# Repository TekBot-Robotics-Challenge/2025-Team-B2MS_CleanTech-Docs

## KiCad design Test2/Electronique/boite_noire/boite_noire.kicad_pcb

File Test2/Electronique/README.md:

# Introduction
Dans les systèmes embarqués modernes, la collecte et l’analyse de données en temps réel sont essentielles pour le suivi et la sécurité des équipements, notamment dans des domaines critiques comme l’automobile, l’aviation ou le ferroviaire. S’inspirant du fonctionnement des boîtes noires utilisées dans ces industries, ce projet a pour objectif de concevoir un système embarqué capable d’enregistrer et de transmettre en temps réel des données de mouvement (vitesse et orientation) à l’aide d’un capteur inertiel. Les informations sont ensuite visualisées sur une station de contrôle via un écran LCD.
Ce projet s’inscrit dans le cadre du Tekbot Robotics Challenge et fait appel à plusieurs compétences majeures : programmation directe des microcontrôleurs ATmega328P sans utiliser de carte Arduino, communication via le protocole I2C, conception de circuits imprimés avec KiCAD, réalisation d’un boîtier cubique de 7 cm, intégration matérielle sur veroboard ou PCB, ainsi que la conception d’une alimentation spécifique.
# Sommaire

- [cahier des charges ](#Cahier-des-charges)
- [Schéma synoptique](#Schéma-synoptique)
- [Réalisation du PCB](#Réalisation-du-PCB)
- [Description fonctionnelle des différents blocs du système](#Description-fonctionnelle-des-différents-blocs-du-système)
- [La communication I2C](#La-communication-I2C)
- [Etapes de validation avant PCB](#Etapes-de-validation-avant-PCB) 
  
# Cahier des charges

## Objectifs fonctionnels
- Lire les données de vitesse et d’orientation à l’aide du MPU6050
- Utiliser le microcontrôleur ATmega328P sans carte Arduino
- Concevoir un circuit imprimé (PCB) et une alimentation autonome
- Transmettre les données à une station de contrôle via I2C
- Afficher les données sur un écran LCD en mode 4 bits

## Contraintes techniques
- Le cube doit mesurer 7x7x7 cm, avec une face ouverte pour voir le circuit
- Le microcontrôleur du cube agit en **maître I2C**
- Le microcontrôleur de la station agit en **esclave I2C**
- Alimentation externe obligatoire, hors du cube
- Schéma et PCB réalisés avec **KiCad**

## Matériel utilisé

- [ATmega328P](https://ww1.microchip.com/downloads/en/DeviceDoc/Atmel-7810-Automotive-Microcontrollers-ATmega328P_Datasheet.pdf) ×2  
- [MPU6050](https://invensense.tdk.com/wp-content/uploads/2015/02/MPU-6000-Datasheet1.pdf)  
- [LCD 16x2 (mode 4 bits)](https://www.gotronic.fr/pj2-sbc-lcd16x2-fr-1441.pdf?srsltid=AfmBOopmg8VyH8PQXxRcqE7GEvoyRwGRHeKVU9ZsKwGmKu13oZXhPhaJ)  
- Alimentation

# Schéma synoptique
Ce système embarqué est composé de deux unités : une boîte noire et une station de contrôle, connectées via le bus I2C. La boîte noire comprend un capteur MPU6050 qui détecte les mouvements de la main et envoie les données à un microcontrôleur ATmega328P configuré en maître. Celui-ci traite les données et les transmet à la station de contrôle, où un autre ATmega328P, configuré en esclave, les reçoit. Les informations sont ensuite affichées sur un écran LCD. Chaque unité est alimentée séparément par une source de 5V.

# Description fonctionnelle des différents blocs du système
## Bloc d’alimentation
## 1. Fonction principale
Ce bloc a pour objectif de fournir une tension continue et stable de 5V nécessaire au fonctionnement des différents composants électroniques du système, notamment le capteur MPU6050, les microcontrôleurs ATmega328P et l'écran LCD.
## 2. Fonctionnement
On utilise trois batteries de Li-Ion 3,7V rechargeables montées en série pour obtenir environ 12V.  
Le régulateur L7805 reçoit ce 12V en entrée (Vin) et fournit du 5V en sortie (Vout).  
Deux condensateurs (330nF et 100nF) sont utilisés pour stabiliser la tension et filtrer les parasites.
- 330nF à l’entrée
- 100nF à la sortie

📌 Le schéma suivant illustre ce montage :

   La simulation sur proteus 
   Les condensateurs de filtrage ont été omis dans ce schéma pour simplifier la représentation, bien qu’ils soient indispensables en pratique pour assurer la stabilité et réduire le bruit.

## Bloc d’entrée(dans la boite noire)

Nous avons choisi le capteur MPU6050 parce qu’il intègre un accéléromètre et un gyroscope dans un seul composant. Cela permet de mesurer les mouvements et les rotations de la main avec précision. Il est facile à utiliser grâce au protocole I2C, et il fonctionne bien avec le microcontrôleur ATmega328P. En plus, il est peu coûteux et largement utilisé dans les projets embarqués. D’autres capteurs peuvent faire un travail similaire, comme le MPU9250 (qui ajoute un magnétomètre), le LSM6DS3 (plus récent et plus économe), ou le ADXL34

## Bloc de commande(dans la boite noire)
### 🛠️ Étape 1 : Prise en main du microcontrôleur ATmega328P

Avant de démarrer le système complet, l’équipe s’est d’abord focalisée sur le microcontrôleur ATmega328P. L’objectif était de comprendre pleinement sa structure interne, ses broches, ainsi que la manière de le configurer et de le simuler.

Nous avons étudié ses principales caractéristiques et son brochage :

- Le format DIP à 28 broches, comme dans les cartes Arduino Uno
- Les broches d’E/S numériques D0 à D13, pour piloter des LED, relais, etc.
- Les entrées analogiques A0 à A5, pour la lecture de capteurs
- L’interface I2C via SDA (PC4) et SCL (PC5)
- La communication série UART via TX (PD1) et RX (PD0)
- Les broches d’alimentation : VCC, GND, AVCC, AREF
- La broche RESET, généralement tirée à l’état haut via une résistance
- Les broches XTAL1/XTAL2 pour le quartz (utilisé plus tard)

Ces éléments nous ont permis de préparer une simulation fiable sous Proteus pour la suite du projet.

### 🧪 Étape 2 : Simulation basique de l’ATmega328P dans Proteus

Après avoir étudié la configuration du microcontrôleur, nous avons réalisé une première simulation simple sous Proteus, afin de valider son fonctionnement dans un environnement simulé.

À ce stade :

- Nous n'avons pas utilisé les connexions d’alimentation (VCC/AVCC) ni de quartz externe, car elles ne sont pas obligatoires pour les logiques simples dans Proteus.
- Nous nous sommes concentrés sur le comportement des broches dans un exemple réel.

#### Scénario de simulation :
Nous avons conçu un système simple dans lequel :

- Un bouton poussoir est connecté à une entrée numérique.
- Lorsqu’on appuie sur le bouton, l’ATmega active un relais via une sortie numérique.
- Ce relais commande une lampe LED 12V, simulant une charge réelle.

Le code Arduino correspondant a été compilé dans l’IDE Arduino, puis le fichier .hex généré a été intégré dans Proteus pour tester le comportement du circuit.

https://github.com/user-attachments/assets/d1cc5dd5-9109-4822-be6e-245693643c00
#### Observations :
- Lorsque le bouton est pressé, le relais s’active et allume la LED.
- Le comportement observé est conforme à la logique attendue et cohérente.
## Bloc d’affichage de la station du controle
Pour l’affichage des données au niveau de la station de contrôle, nous avons opté pour un écran LCD équipé d’un module I2C. Ce choix permet de simplifier le montage électronique en réduisant considérablement le nombre de connexions nécessaires entre le microcontrôleur et l’écran. Grâce à cette interface, seules deux lignes (SDA et SCL) suffisent pour transmettre les informations, ce qui laisse davantage de broches disponibles pour d’autres composants. L’écran LCD I2C assure ainsi une lecture claire et en temps réel des données de vitesse et d’orientation envoyées par la boîte noire.  

# La communication I2C
Ce document constitue une présentation détaillée et approfondie du protocole **I2C (Inter-Integrated Circuit)**, qui est un standard de communication série synchrone très répandu dans l’électronique embarquée. Ce protocole facilite l’échange d’informations entre un ou plusieurs maîtres et plusieurs périphériques esclaves en utilisant seulement deux fils, simplifiant ainsi les connexions matérielles tout en assurant une communication fiable et efficace.  

## ⚙️ Principe de fonctionnement
[Protocole I2C](https://fr.wikipedia.org/wiki/I2C) (Inter-Integrated Circuit), développé par Philips (aujourd’hui NXP) dans les années 1980, est un standard mondial pour la communication série entre circuits intégrés, surtout dans les systèmes embarqués. Il utilise un bus bidirectionnel à deux fils : SDA pour les données et SCL pour l’horloge, permettant à plusieurs périphériques de partager le même canal tout en gérant précisément l’accès.  
Contrairement à des protocoles comme SPI, I2C minimise le nombre de connexions nécessaires, ce qui simplifie le routage sur circuit imprimé et réduit les coûts.   Ce protocole est largement utilisé dans des domaines variés : automobile, domotique, informatique, etc.  
I2C fonctionne selon un modèle.[maître-esclave](https://www.ionos.fr/digitalguide/serveur/know-how/le-principe-master/slave): un ou plusieurs maîtres contrôlent la communication, et les esclaves répondent aux requêtes. Chaque communication commence par une condition **Start**, suivie de **l’adresse de l’esclave** et d’un bit de direction (lecture/écriture). Les données sont ensuite échangées octet par octet, chaque octet étant confirmé par **un bit d’acquittement**(ACK). La communication se termine par une condition **Stop**, qui libère le bus.  
Techniquement, I2C utilise des lignes ouvertes (open-drain) : les dispositifs ne peuvent que tirer les lignes vers le bas, tandis que des résistances pull-up maintiennent le niveau haut par défaut. Cela évite les conflits, notamment en mode multi-maîtres.  
Enfin, I2C offre une grande flexibilité en termes de vitesse, du mode standard (100 kHz) au mode rapide (jusqu’à 3,4 MHz) et au-delà dans certaines variantes propriétaires.  

### 🔹 Prise de contrôle du bus

La prise de contrôle du bus par un maître débute par une **condition Start (S)**, qui est un événement distinctif sur le bus. Cette condition correspond à une transition sur la ligne SDA de l’état haut à l’état bas, alors que la ligne SCL est maintenue à l’état haut. Cette séquence particulière est détectée par tous les périphériques connectés au bus, qui entrent alors en mode écoute, prêts à recevoir des données.  

La condition Start joue un rôle fondamental : elle marque l’exclusivité du maître sur le bus, ce qui évite les collisions ou l’interférence avec d’autres maîtres éventuels. Elle sert aussi de synchronisation initiale à la transmission de données, en assurant que tous les appareils sont synchronisés sur le début de la communication.  

Les résistances pull-up sur les lignes SDA et SCL maintiennent ces lignes à un état logique haut par défaut, garantissant ainsi que le bus est en repos quand aucune communication n’a lieu.

## 🖼️ Image : BUS I2C 

## 🖼️ Image : condition start

---

### 🔹 Transmission d'un octet

La transmission des données sur le bus I2C s’effectue par octets (8 bits). Chaque bit est transmis séquentiellement, en commençant par le bit le plus significatif (MSB).  

Le protocole impose que chaque bit soit placé sur la ligne SDA pendant que la ligne SCL est à l’état bas. Ensuite, la ligne SCL passe à l’état haut, moment où le récepteur lit la valeur présente sur la ligne SDA. Lorsque la ligne SCL redescend à l’état bas, l’émetteur peut placer le bit suivant sur SDA, et ainsi de suite.  

Après l’envoi des 8 bits d’un octet, la ligne SDA est libérée pendant le 9e cycle d’horloge. C’est alors au récepteur de signaler par un bit d’acquittement (ACK) s’il a correctement reçu l’octet, en tirant la ligne SDA à l’état bas. S’il ne tire pas SDA à zéro, un bit de non-acquittement (NACK) est détecté, ce qui indique que la communication doit être interrompue ou qu’une erreur s’est produite.  

Ce mécanisme d’**ACK/NACK** est crucial car il assure la fiabilité des transmissions, permettant au maître de savoir si l’esclave est disponible et prêt à recevoir ou envoyer des données.

---

### 🔹 Transmission d'une adresse

Après la condition Start, le maître envoie un octet d’adresse pour identifier l’esclave avec lequel il souhaite communiquer. L’adresse est généralement codée sur 7 bits, suivis d’un bit R/W indiquant si la transaction sera une lecture ou une écriture.  

Le protocole prévoit aussi une extension 10 bits pour les réseaux comportant un grand nombre de périphériques, mais cette extension est moins fréquemment utilisée.  

Tous les périphériques esclaves surveillent le bus et comparent l’adresse reçue avec leur propre adresse. Celui qui reconnaît son adresse répond alors par un bit ACK en tirant la ligne SDA à l’état bas pendant le 9e bit. Les autres esclaves restent silencieux jusqu’à la prochaine séquence.  

Cette étape est essentielle car elle garantit que seules les communications destinées à un périphérique spécifique sont traitées, évitant ainsi toute interférence entre plusieurs périphériques sur le même bus.
## 🖼️ Image : transmission d'une adresse  

---

### 🔹 Écriture d'une donnée

Une fois l’adresse reconnue par l’esclave, la phase de transfert des données peut commencer. Le maître transmet alors les octets de données à l’esclave, chaque octet étant suivi d’un bit ACK envoyé par l’esclave pour confirmer la bonne réception.  

Le protocole permet d’envoyer autant d’octets que nécessaire dans une même communication, ce qui permet des transferts efficaces et continus.  

Pour terminer la communication, le maître génère une condition **Stop (P)**, qui correspond à une transition de la ligne SDA de l’état bas à l’état haut alors que la ligne SCL est haute. Cette séquence indique à tous les périphériques que la transmission est terminée et que le bus est libéré pour une autre communication.  

Il existe également une condition **Restart**, qui est une condition Start générée sans condition Stop préalable, permettant de chaîner plusieurs opérations sur le même bus sans interruption.  
## 🖼️ Image : transmission d'une donnee

## 🖼️ Image : condition stop

---

### 🔹 Arbitration

Le protocole I2C est conçu pour supporter un mode multi-maîtres, où plusieurs maîtres peuvent tenter d’accéder au bus simultanément. Pour éviter les conflits, un mécanisme d’arbitrage est mis en place.  

Lorsqu’un maître commence à transmettre, il surveille la ligne SDA et la compare avec ce qu’il souhaite envoyer. Si un maître détecte que la ligne SDA est forcée à l’état bas par un autre maître alors qu’il tente de la maintenir haute, il comprend qu’il a perdu l’arbitrage et abandonne immédiatement la transmission, laissant le bus libre au maître dominant.  

Ce mécanisme garantit qu’aucune collision électrique ne se produit sur le bus et que seule une source transmet à un instant donné. C’est une des forces du protocole I2C, qui permet une coexistence harmonieuse de plusieurs maîtres sur un même bus.
## 🖼️ Image : arbitrage

### 🔹 Clock Stretching

Le clock stretching est une fonctionnalité du protocole I2C qui permet à un esclave de ralentir temporairement la communication lorsqu’il n’est pas prêt à envoyer ou recevoir des données. Cela se fait en gardant la ligne SCL à l’état bas (LOW), empêchant ainsi le maître de continuer à envoyer des impulsions d’horloge. Une fois que l’esclave est prêt, il libère la ligne SCL, permettant au maître de reprendre la transmission. Cette technique est utile, par exemple, lorsque le capteur a besoin de plus de temps pour traiter ou préparer les données. Le maître doit respecter cet étirement d’horloge pour éviter des erreurs de communication.  

## 🖼️ Image : clock stretching

---
## 📡 Communication I2C entre MPU6050 et ATmega328P
Dans notre projet, le microcontrôleur **ATmega328P** communique avec le capteur **MPU6050** à l’aide du protocole **I2C**. Ce protocole permet de transmettre les données d’accélération et de rotation via deux fils (`SDA` et `SCL`). Le **MPU6050** agit comme **esclave**, et l’**ATmega328P** comme **maître**.

---

### 🔹 Fonctionnement de la liaison I2C

La connexion matérielle entre le MPU6050 et l’ATmega328P s’effectue via le protocole I2C (Inter-Integrated Circuit), qui utilise deux lignes de communication :   
- SDA (Serial Data Line) : ligne bidirectionnelle pour l’échange des données, connectée à la broche PC4 de l’ATmega328P.    
- SCL (Serial Clock Line) : ligne d’horloge générée par le maître, connectée à la broche PC5 de l’ATmega328P.

Sur le bus I2C, le dispositif qui initie la communication est appelé maître, tandis que celui qui répond s’appelle esclave. Dans notre cas :    
L’ATmega328P joue le rôle de maître, c’est lui qui contrôle le bus, génère l’horloge, et initie les échanges.    
Le MPU6050 est l’esclave, il attend que le maître lui demande des données spécifiques.    
Le maître démarre la communication en envoyant une adresse unique correspondant à l’esclave (ici l’adresse I2C du MPU6050, généralement 0x68), suivie d’une commande indiquant quel registre ou donnée il souhaite lire.  
                          
| ATmega328P | MPU6050 |
|------------|---------|
| PC4 (SDA)    | SDA     |
| PC5 (SCL)    | SCL     |
| VCC        | 5V  |
| GND        | GND     |
| 🔧 Pull-up | Recommandé : 4.7kΩ sur SDA et SCL |  

## 🖼️ Image : liaison-i2c-entre-mpu6050-et-atmega328p

---

### 🔹 Envoi des commandes et réception des données

La communication suit ce processus :  
- Le maître (ATmega328P) commence par envoyer une commande au MPU6050, qui consiste à spécifier l’adresse du registre interne dont il souhaite lire la valeur. Par exemple, pour lire l’accélération sur l’axe X, il envoie l’adresse du registre ACCEL_XOUT_H.  
- Cette commande est envoyée via le bus I2C sous forme d’une trame contenant l’adresse de l’esclave, suivie de l’adresse du registre ciblé.  
- Une fois la commande reçue, le MPU6050 prépare la donnée correspondante et la transmet dès que le maître la demande.  
- Le maître récupère alors la ou les valeurs envoyées par le capteur, généralement sur plusieurs octets, qu’il traite ensuite pour en extraire l’information de mouvement (accélération, rotation, température).

# Etapes_de_validation_avant_PCB  

## Objectif Général
Avant de réaliser directement le PCB de la boîte noire et de la station de contrôle, nous avons choisi de suivre une démarche progressive. L’objectif était de bien maîtriser la communication I2C et le fonctionnement du microcontrôleur ATmega328P.  
Tester les fonctionnalités sur breadboard avec des composants simples (comme un bouton, une LED, un MPU6050 ou un LCD) permet plus de flexibilité et facilite le débogage. Contrairement au PCB, où les composants sont soudés, la breadboard permet des modifications rapides.  
Cette approche nous a permis de valider chaque étape avant l'intégration finale sur le PCB, en réduisant les risques d’erreurs matérielles ou logicielles.

---

## Étapes de Réalisation 

###  Étape 1 : Communication I2C entre deux Arduino (Test de base)

####  Objectif :
Valider le **fonctionnement de la communication I2C** entre deux microcontrôleurs en utilisant un exemple simple : un bouton poussoir et une LED.

####  Composants utilisés :
- 2 cartes **Arduino UNO** 
- 1 bouton poussoir (sur le maître)  
- 1 LED (sur l’esclave)  
- Câblage SDA/SCL entre les deux cartes  

####  Fonctionnement :
- L’Arduino **maître** lit l’état d’un bouton poussoir connecté en entrée.
- Cet état (appuyé ou relâché) est transmis à l’Arduino **esclave** via le protocole I2C.
- L’esclave reçoit cette donnée et **contrôle une LED** : elle s’allume si le bouton est appuyé, s’éteint sinon.

####  But de l'étape :
- Apprendre à configurer le bus I2C (maître/esclave).
- Vérifier la synchronisation et la fiabilité de la communication.
- Observer une réponse simple à un signal I2C.
  
#### le montage 
( 

#### le resultat
https://github.com/user-attachments/assets/f24d194f-d3f9-40da-8c5a-b3b9a5e75ebc

---

###  Étape 2 : Remplacement par des modules réels (MPU6050 et LCD)

####  Objectif :
Simuler une application plus réaliste en utilisant des **capteurs réels(MPU6050)** et un **afficheur(lCD)**, tout en gardant la communication I2C entre deux cartes.

####  Composants utilisés :
- MPU6050 (capteur accéléromètre/gyroscope) sur le **maître**
- Écran LCD (type I2C 16x2) sur l’**esclave**
- Deux cartes Arduino

####  Fonctionnement :
- Le capteur **MPU6050** collecte les données d’accélération et de rotation.
- Ces données sont lues par l’Arduino **maître** via I2C.
- Le maître envoie ensuite les valeurs traitées à l’**esclave**.
- L’Arduino esclave reçoit les données et les affiche sur le **LCD**.

####  But de l'étape :
- Remplacer des composants de test par des modules **intelligents**.
- Manipuler un **capteur complexe** avec acquisition de données.
- Gérer l'affichage distant d'informations, toujours via I2C.
- Approfondir le protocole I2C dans un cas concret (multi-esclaves potentiels, synchronisation).
- 
#### Le montage

#### Le resultat

https://github.com/user-attachments/assets/1c67d0e5-90eb-4aa1-bebf-cd58e934528a

---

###  Étape 3 : Intégration avec ATmega328P (préparation au PCB)

####  Objectif :
Remplacer la carte Arduino par le **microcontrôleur brut** (ATmega328P), afin de simuler les conditions réelles d’un circuit imprimé.

####  Composants utilisés :
- 2× ATmega328P   
- 2× Quartz   
- 4× Condensateurs 22 pF   
- 1× MPU6050  
- 1× Écran LCD 16x2 avec interface I2C   
- 2× Boutons poussoirs  
- 2× Résistances 10 kΩ   
- Fils de connexion (Dupont)  
- Breadboard  

####  Fonctionnement :
- L’ATmega328P est programmé avec le même code que celui utilisé sur une carte Arduino, à l’aide d’un programmateur externe (comme USBasp ou Arduino as ISP).  
- Les deux ATmega328P communiquent via le protocole I2C :
    - L’un joue le rôle de maître (elle collecte les données du MPU6050).  
    - L’autre joue le rôle d’esclave (elle affiche les données sur un écran LCD I2C).  
- Les microcontrôleurs sont utilisés en mode "standalone" (hors carte de développement) :
- Connectés sur breadboard avec :
    - Un quartz et deux condensateurs 22 pF pour chaque ATMEGA328P pour générer l’horloge.
    - Une alimentation 5V stable.
    - Un bouton poussoir relié à la broche RESET de chaque ATmega.
    - Une résistance de 10 kΩ connectée entre la broche RESET et VCC, pour garantir un redémarrage stable.

####  But de l'étape :
- S’assurer que le microcontrôleur fonctionne correctement en **mode autonome**.
- Tester la communication I2C dans les **conditions matérielles réelles** du futur PCB.
- Préparer l’intégration finale des composants sur un **PCB personnalisé**.

####  Le montage

####  Le resultat
[la video](https://github.com/user-attachments/assets/9b0e3092-58c1-435a-8556-9573676f7728)  

---

##  Pourquoi cette Démarche ?
La réalisation d’un PCB nécessite des choix précis de composants et un bon fonctionnement garanti **en amont**. Cette démarche par étapes nous a permis de :

- Identifier les erreurs éventuelles (bruit sur la ligne I2C, mauvais câblage, alimentation instable…).
- Tester progressivement les modules dans un environnement de développement.
- Réduire le risque d’erreur lors de la conception du PCB.
- Avoir une base fonctionnelle avant le passage à la fabrication.

 # Réalisation du PCB
# premiere PCB (Boite noire)
## Création du schéma électronique
- Conception du schéma intégrant le microcontrôleur ATmega328P, le capteur MPU-6050 et les connecteurs.

## Affectation des empreintes (footprints)
- Attribution des empreintes physiques correspondant aux composants.

## Organisation du PCB
- Ajustement de la disposition pour optimiser l’espace et faciliter le routage.

## Routage des pistes
#### Introduction : Routage automatique avec FreeRouting
Pour la phase de routage de mon circuit imprimé, j’ai utilisé un routage automatique à l’aide de l’application FreeRouting. Ce choix m’a permis de gagner du temps, d’obtenir un routage optimisé, et de réduire les erreurs humaines dans le placement des pistes.  
FreeRouting est un outil open source externe à KiCad, capable d’analyser les connexions (netlist) et de générer un routage respectant les règles de design (DRC). Il offre plusieurs avantages :  
•	🔹 Optimisation automatique des longueurs et des croisements de pistes  
•	🔹 Respect des règles de clearance et de largeur de pistes  
•	🔹 Visualisation rapide des pistes critiques et des contraintes  
•	🔹 Gain de temps par rapport au routage manuel complet  
Le routage généré a ensuite été importé dans KiCad pour la vérification finale et l’inspection des règles électriques (DRC).  

## Définition des contours du PCB (Edge Cuts)
- Délimitation de la forme finale et des dimensions de la carte. 

## Verificaton des erreurs (DRC)

## Visualisation 3D du PCB
- Contrôle visuel du circuit imprimé en trois dimensions avant fabrication.  

https://github.com/user-attachments/assets/f897ede6-44c2-42a2-96d0-31dc648d50c1  

# Deuxieme PCB( Station de contole )
## Création du schéma électronique  
- Conception du schéma intégrant le microcontrôleur ATmega328P, lcd et les connecteurs

## Anotation  
  
## Correction des erreurs  
  
## Footprints  
  
## Organisation du PCB  
  
## Définition des contours du PCB (Edge Cuts)  
  
## Plan de masse GND  
  
## Routage
  
## Visualisation 3D du PCB

https://github.com/user-attachments/assets/c5784cd8-9c96-4c7d-97fa-074df501b6cc

## Préparation physique du Véloboard : composants soudés  

 https://github.com/user-attachments/assets/31437a9f-915f-4c3a-84a9-cc7a7483c2a1

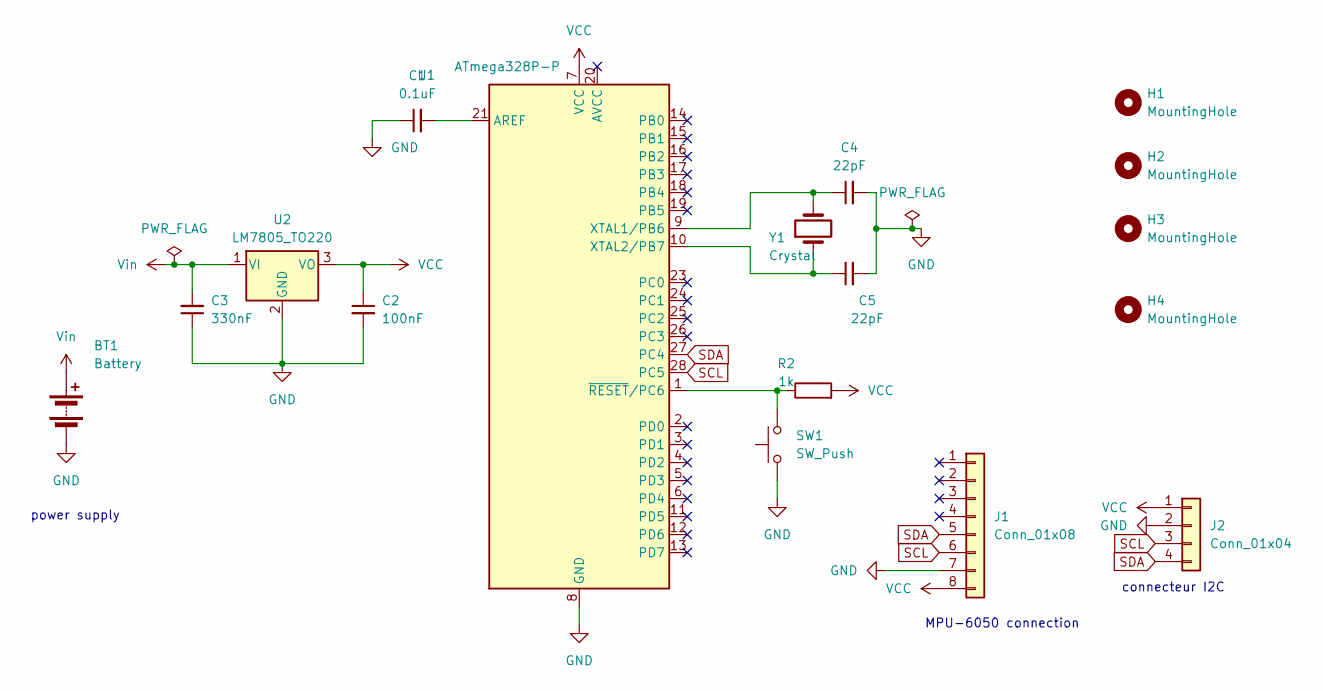
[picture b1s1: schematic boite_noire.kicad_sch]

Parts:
BT1: Battery; TerminalBlock_bornier-2_P5.08mm
C1: 0.1uF; C_Disc_D3.0mm_W1.6mm_P2.50mm
C2: 100nF; C_Disc_D3.0mm_W1.6mm_P2.50mm
C3: 330nF; C_Disc_D3.0mm_W1.6mm_P2.50mm
C4, C5: 22pF; C_Disc_D3.0mm_W1.6mm_P2.50mm
H1, H2, H3, H4: MountingHole; MountingHole_2.1mm
J1: Conn_01x08; PinSocket_1x08_P1.00mm_Vertical
J2: Conn_01x04; PinHeader_1x04_P1.00mm_Vertical
R2: 1k; R_Axial_DIN0204_L3.6mm_D1.6mm_P5.08mm_Horizontal
SW1: SW_Push; SW_PUSH_6mm
U1: ATmega328P-P; DIP-28_W7.62mm
U2: LM7805_TO220; TO-220-3_Vertical
Y1: Crystal; Crystal_AT310_D3.0mm_L10.0mm_Horizontal

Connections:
GND: BT1.2 (-), C1.1, C2.2, C3.1, C4.2, C5.2, J1.7, J2.2, SW1.1, U1.8 (GND), U1.22 (GND), U2.2 (GND)
unnamed: C1.2, U1.21 (AREF)
unnamed: C4.1, U1.9 (XTAL1/PB6), Y1.2
unnamed: C5.1, U1.10 (XTAL2/PB7), Y1.1
unnamed: R2.1, SW1.2, U1.1 (~RESET/PC6)
SCL: J1.6, J2.3, U1.28 (PC5)
SDA: J1.5, J2.4, U1.27 (PC4)
VCC: C2.1, J1.8, J2.1, R2.2, U1.7 (VCC), U2.3 (VO)
Vin: BT1.1 (+), C3.2, U2.1 (VI)

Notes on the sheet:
MPU-6050 connection
connecteur I2C
power supply

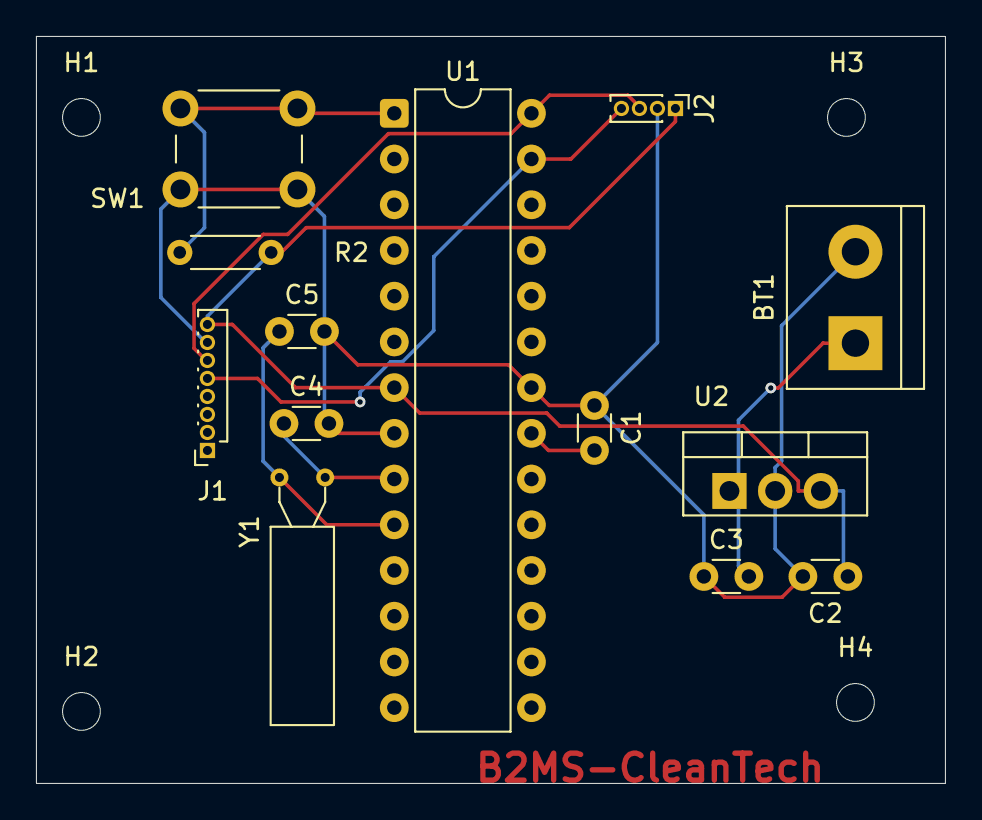
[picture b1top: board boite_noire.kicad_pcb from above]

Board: 2 copper layers, 50.5 x 41.5 mm, 17 parts (0 on the bottom side), 9 nets.

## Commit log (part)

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2025-06-14 adding videos
2025-06-14 changes code's display
2025-06-14 change code's display
2025-06-14 adjusting motion
2025-06-15 adding reset display
2025-06-19 test2 update
2025-06-19 adding bonus for test2
2025-06-19 adding video for bonus
2025-06-26 adding test3
2025-06-28 adding tekbot_navigation
2025-06-28 adding video demo_final.mp4
2025-06-28 adding images
2025-06-28 update format code
2025-06-28 Update with final demonstrationtest3
2025-06-28 changes interfaces
2025-06-28 correction of masse test3
2025-07-02 adding images
    it, mecanique, electronic, convoyeur
2025-07-02 changing mechatronic to conveyor
2025-07-02 Update mechatronic to conveyor
2025-07-02 mechatronic to conveyor
2025-07-08 adjusting text format
2025-07-08 reorganisation
2025-07-08 adjusting format
2025-07-11 adjusting scroll and navigation
2025-07-12 adding convoyeur.html
2025-07-24 Update partie mecanique
2025-07-26 Create read
2025-07-26 adjusting timing scroll
2025-08-15 adding pcb.zip
2025-08-15 adding more explnation
2025-08-15 modifying ressources link
2025-08-15 More explanation
2025-08-16 Adding further explanation
2026-02-27 Add yolov5_statique.mp4
2026-02-27 Add B2MS_detection.ipynb
2026-02-27 Add Logiciels.zip
2026-02-27 Add b2ms_ramassage.zip
2026-02-27 Add b2ms_Dofbot_IA.zip
2026-02-27 Add 2000_labeled_images_for_YOLO.zip
2026-02-28 Add yolov5_pytorch_training.zip
2026-02-28 Add ressources_images.zip
2026-02-28 Add jetson_dofbot.zip
2026-02-28 Add b2ms_classification.zip
2026-03-01 Add b2ms_YOLOv5nu.zip
2026-03-01 Add b2ms_YOLOv8n.zip
2026-03-06 Remove .mp4 from LFS tracking in .gitattributes
2026-06-09 modif video sensorColor_rgb
2026-06-09 colorpal en ts12
